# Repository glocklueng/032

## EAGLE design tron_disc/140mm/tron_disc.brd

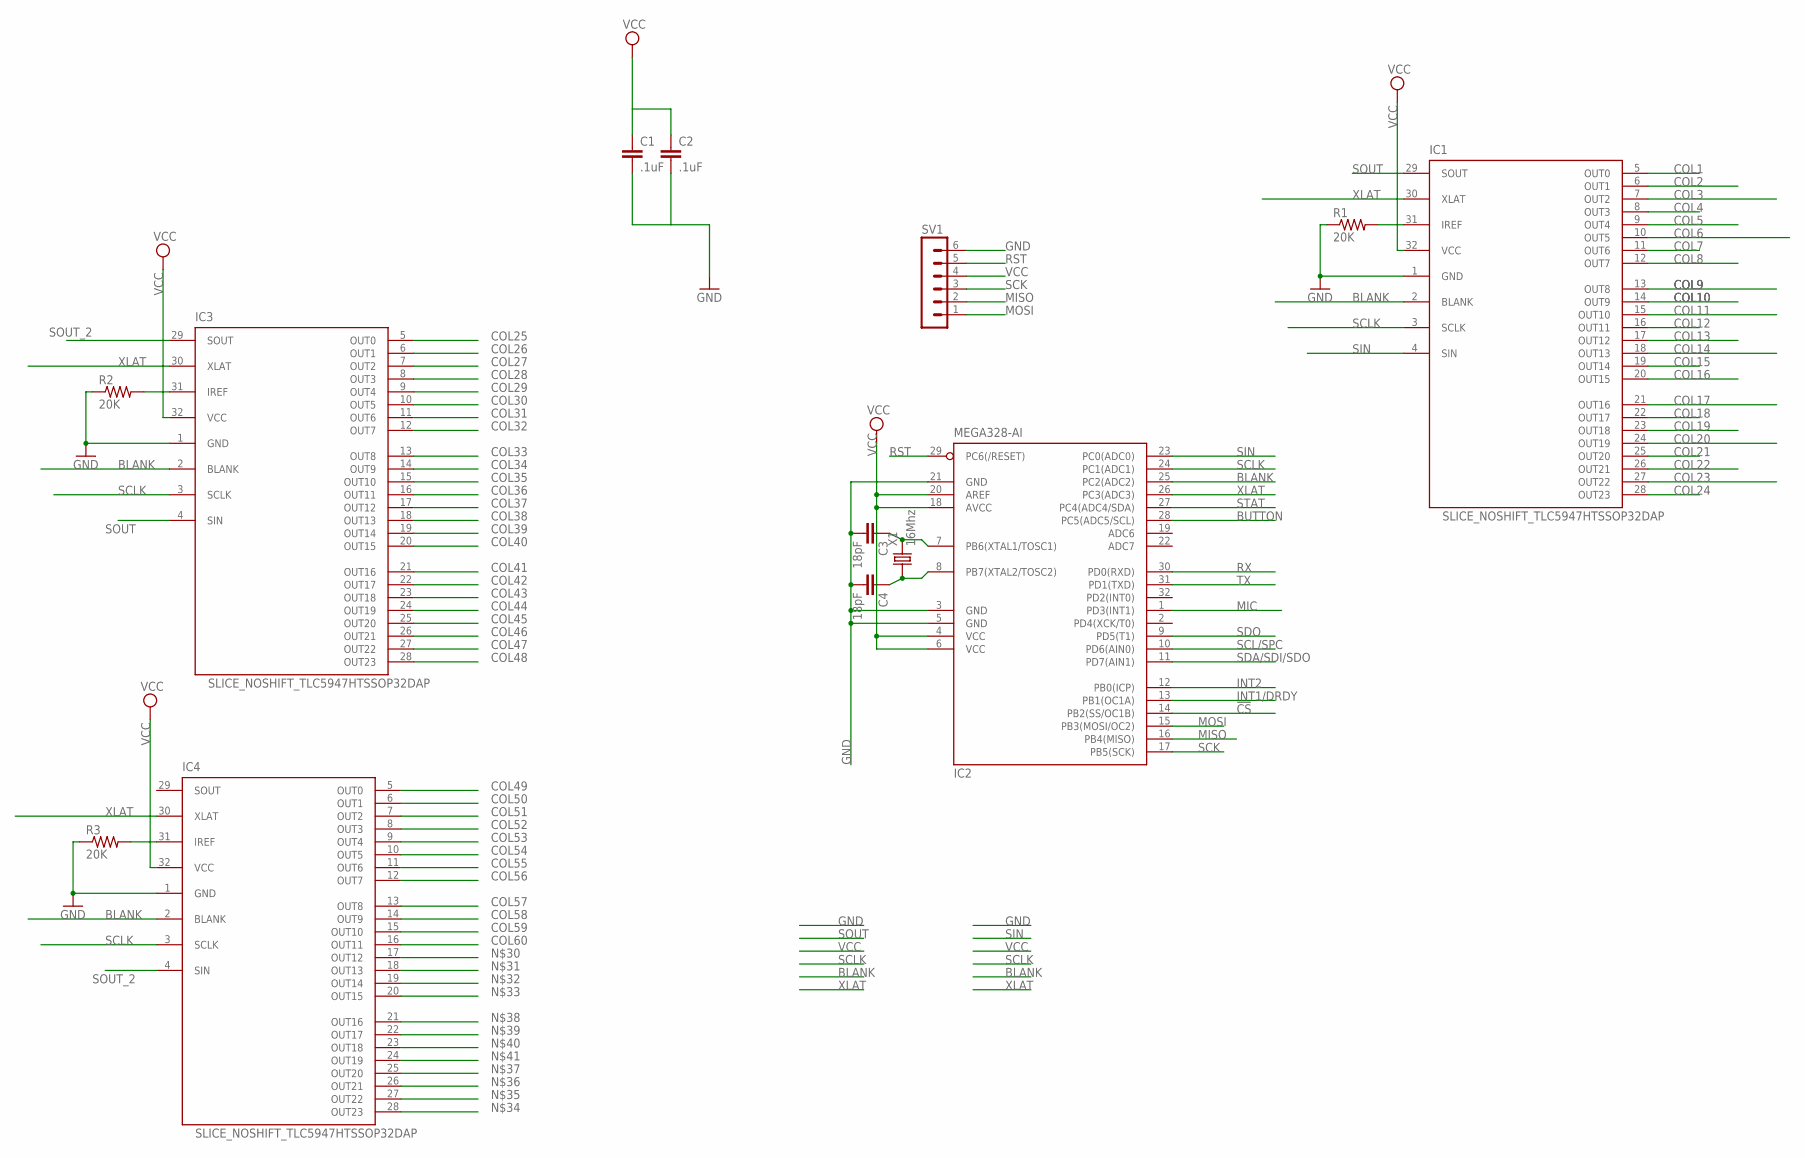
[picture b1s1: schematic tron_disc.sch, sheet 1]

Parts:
C1, C2: .1uF; 0805
C3, C4: 18pF; 0805
IC1, IC3, IC4: SLICE_NOSHIFT_TLC5947HTSSOP32DAP; HTSSOP32DAP
IC2: MEGA328-AI; TQFP32-08
R1, R2, R3: 20K; R0805
SV1: MA06-1
X1: 16Mhz; 5032

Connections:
!CS: IC2.14 (PB2(SS/OC1B))
BLANK: IC1.2 (BLANK), IC2.25 (PC2(ADC2)), IC3.2 (BLANK), IC4.2 (BLANK)
BUTTON: IC2.28 (PC5(ADC5/SCL)); also elsewhere on the board
COL1: IC1.5 (OUT0); also elsewhere on the board
COL2: IC1.6 (OUT1); also elsewhere on the board
COL3: IC1.7 (OUT2); also elsewhere on the board
COL4: IC1.8 (OUT3); also elsewhere on the board
COL5: IC1.9 (OUT4); also elsewhere on the board
COL6: IC1.10 (OUT5); also elsewhere on the board
COL7: IC1.11 (OUT6); also elsewhere on the board
COL8: IC1.12 (OUT7); also elsewhere on the board
COL9: IC1.13 (OUT8); also elsewhere on the board
COL10: IC1.14 (OUT9); also elsewhere on the board
COL11: IC1.15 (OUT10); also elsewhere on the board
COL12: IC1.16 (OUT11); also elsewhere on the board
COL13: IC1.17 (OUT12); also elsewhere on the board
COL14: IC1.18 (OUT13); also elsewhere on the board
COL15: IC1.19 (OUT14); also elsewhere on the board
COL16: IC1.20 (OUT15); also elsewhere on the board
COL17: IC1.21 (OUT16); also elsewhere on the board
COL18: IC1.22 (OUT17); also elsewhere on the board
COL19: IC1.23 (OUT18); also elsewhere on the board
COL20: IC1.24 (OUT19); also elsewhere on the board
COL21: IC1.25 (OUT20); also elsewhere on the board
COL22: IC1.26 (OUT21); also elsewhere on the board
COL23: IC1.27 (OUT22); also elsewhere on the board
COL24: IC1.28 (OUT23); also elsewhere on the board
COL25: IC3.5 (OUT0); also elsewhere on the board
COL26: IC3.6 (OUT1); also elsewhere on the board
COL27: IC3.7 (OUT2); also elsewhere on the board
COL28: IC3.8 (OUT3); also elsewhere on the board
COL29: IC3.9 (OUT4); also elsewhere on the board
COL30: IC3.10 (OUT5); also elsewhere on the board
COL31: IC3.11 (OUT6); also elsewhere on the board
COL32: IC3.12 (OUT7); also elsewhere on the board
COL33: IC3.13 (OUT8); also elsewhere on the board
COL34: IC3.14 (OUT9); also elsewhere on the board
COL35: IC3.15 (OUT10); also elsewhere on the board
COL36: IC3.16 (OUT11); also elsewhere on the board
COL37: IC3.17 (OUT12); also elsewhere on the board
COL38: IC3.18 (OUT13); also elsewhere on the board
COL39: IC3.19 (OUT14); also elsewhere on the board
COL40: IC3.20 (OUT15); also elsewhere on the board
COL41: IC3.21 (OUT16); also elsewhere on the board
COL42: IC3.22 (OUT17); also elsewhere on the board
COL43: IC3.23 (OUT18); also elsewhere on the board
COL44: IC3.24 (OUT19); also elsewhere on the board
COL45: IC3.25 (OUT20); also elsewhere on the board
COL46: IC3.26 (OUT21); also elsewhere on the board
COL47: IC3.27 (OUT22); also elsewhere on the board
COL48: IC3.28 (OUT23); also elsewhere on the board
COL49: IC4.5 (OUT0); also elsewhere on the board
COL50: IC4.6 (OUT1); also elsewhere on the board
COL51: IC4.7 (OUT2); also elsewhere on the board
COL52: IC4.8 (OUT3); also elsewhere on the board
COL53: IC4.9 (OUT4); also elsewhere on the board
COL54: IC4.10 (OUT5); also elsewhere on the board
COL55: IC4.11 (OUT6); also elsewhere on the board
COL56: IC4.12 (OUT7); also elsewhere on the board
COL57: IC4.13 (OUT8); also elsewhere on the board
COL58: IC4.14 (OUT9); also elsewhere on the board
COL59: IC4.15 (OUT10); also elsewhere on the board
COL60: IC4.16 (OUT11); also elsewhere on the board
GND: C1.2, C2.2, C3.2, C4.2, IC1.1 (GND), IC2.3 (GND), IC2.5 (GND), IC2.21 (GND), IC3.1 (GND), IC4.1 (GND), R1.1, R2.1, R3.1, SV1.6; also elsewhere on the board
INT1/DRDY: IC2.13 (PB1(OC1A))
INT2: IC2.12 (PB0(ICP))
MIC: IC2.1 (PD3(INT1))
MISO: IC2.16 (PB4(MISO)), SV1.2
MOSI: IC2.15 (PB3(MOSI/OC2)), SV1.1
unnamed: IC3.31 (IREF), R2.2
unnamed: C3.1, IC2.7 (PB6(XTAL1/TOSC1)), X1.2
unnamed: C4.1, IC2.8 (PB7(XTAL2/TOSC2)), X1.1
unnamed: IC1.31 (IREF), R1.2
unnamed: IC4.31 (IREF), R3.2
RST: IC2.29 (PC6(/RESET)), SV1.5; also elsewhere on the board
RX: IC2.30 (PD0(RXD))
SCK: IC2.17 (PB5(SCK)), SV1.3
SCL/SPC: IC2.10 (PD6(AIN0))
SCLK: IC1.3 (SCLK), IC2.24 (PC1(ADC1)), IC3.3 (SCLK), IC4.3 (SCLK)
SDA/SDI/SDO: IC2.11 (PD7(AIN1))
SDO: IC2.9 (PD5(T1))
SIN: IC1.4 (SIN), IC2.23 (PC0(ADC0))
SOUT: IC1.29 (SOUT), IC3.4 (SIN)
SOUT_2: IC3.29 (SOUT), IC4.4 (SIN)
STAT: IC2.27 (PC4(ADC4/SDA))
TX: IC2.31 (PD1(TXD))
VCC: C1.1, C2.1, IC1.32 (VCC), IC2.4 (VCC), IC2.6 (VCC), IC2.18 (AVCC), IC2.20 (AREF), IC3.32 (VCC), IC4.32 (VCC), SV1.4; also elsewhere on the board
XLAT: IC1.30 (XLAT), IC2.26 (PC3(ADC3)), IC3.30 (XLAT), IC4.30 (XLAT)

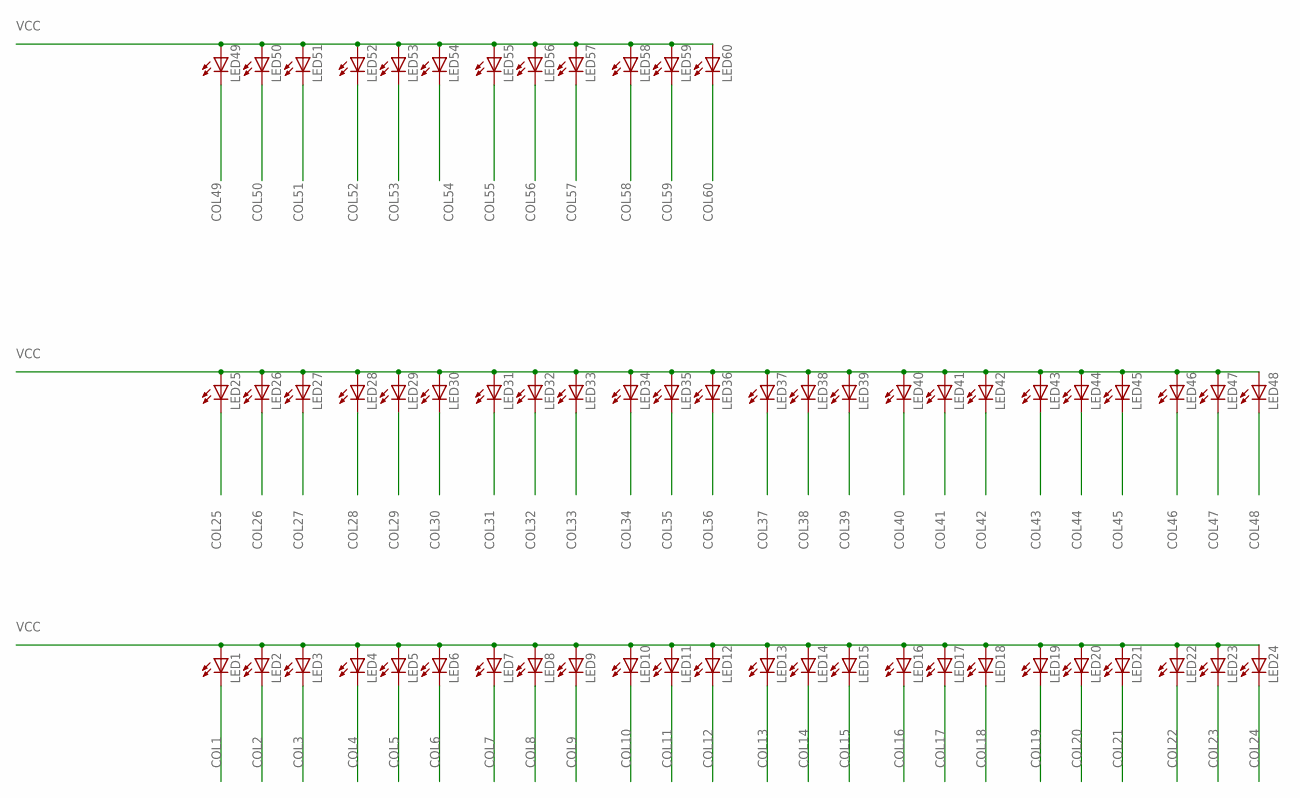
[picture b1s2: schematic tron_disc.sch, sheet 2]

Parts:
LED1, LED2, LED3, LED4, LED5, LED6, LED7, LED8, LED9, LED10, LED11, LED12, LED13, LED14, LED15, LED16, LED17, LED18, LED19, LED20, LED21, LED22, LED23, LED24, LED25, LED26, LED27, LED28, LED29, LED30, LED31, LED32, LED33, LED34, LED35, LED36, LED37, LED38, LED39, LED40, LED41, LED42, LED43, LED44, LED45, LED46, LED47, LED48, LED49, LED50, LED51, LED52, LED53, LED54, LED55, LED56, LED57, LED58, LED59, LED60: LEDCHIPLED_1206; CHIPLED_1206

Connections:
COL1: LED1.C; also elsewhere on the board
COL2: LED2.C; also elsewhere on the board
COL3: LED3.C; also elsewhere on the board
COL4: LED4.C; also elsewhere on the board
COL5: LED5.C; also elsewhere on the board
COL6: LED6.C; also elsewhere on the board
COL7: LED7.C; also elsewhere on the board
COL8: LED8.C; also elsewhere on the board
COL9: LED9.C; also elsewhere on the board
COL10: LED10.C; also elsewhere on the board
COL11: LED11.C; also elsewhere on the board
COL12: LED12.C; also elsewhere on the board
COL13: LED13.C; also elsewhere on the board
COL14: LED14.C; also elsewhere on the board
COL15: LED15.C; also elsewhere on the board
COL16: LED16.C; also elsewhere on the board
COL17: LED17.C; also elsewhere on the board
COL18: LED18.C; also elsewhere on the board
COL19: LED19.C; also elsewhere on the board
COL20: LED20.C; also elsewhere on the board
COL21: LED21.C; also elsewhere on the board
COL22: LED22.C; also elsewhere on the board
COL23: LED23.C; also elsewhere on the board
COL24: LED24.C; also elsewhere on the board
COL25: LED25.C; also elsewhere on the board
COL26: LED26.C; also elsewhere on the board
COL27: LED27.C; also elsewhere on the board
COL28: LED28.C; also elsewhere on the board
COL29: LED29.C; also elsewhere on the board
COL30: LED30.C; also elsewhere on the board
COL31: LED31.C; also elsewhere on the board
COL32: LED32.C; also elsewhere on the board
COL33: LED33.C; also elsewhere on the board
COL34: LED34.C; also elsewhere on the board
COL35: LED35.C; also elsewhere on the board
COL36: LED36.C; also elsewhere on the board
COL37: LED37.C; also elsewhere on the board
COL38: LED38.C; also elsewhere on the board
COL39: LED39.C; also elsewhere on the board
COL40: LED40.C; also elsewhere on the board
COL41: LED41.C; also elsewhere on the board
COL42: LED42.C; also elsewhere on the board
COL43: LED43.C; also elsewhere on the board
COL44: LED44.C; also elsewhere on the board
COL45: LED45.C; also elsewhere on the board
COL46: LED46.C; also elsewhere on the board
COL47: LED47.C; also elsewhere on the board
COL48: LED48.C; also elsewhere on the board
COL49: LED49.C; also elsewhere on the board
COL50: LED50.C; also elsewhere on the board
COL51: LED51.C; also elsewhere on the board
COL52: LED52.C; also elsewhere on the board
COL53: LED53.C; also elsewhere on the board
COL54: LED54.C; also elsewhere on the board
COL55: LED55.C; also elsewhere on the board
COL56: LED56.C; also elsewhere on the board
COL57: LED57.C; also elsewhere on the board
COL58: LED58.C; also elsewhere on the board
COL59: LED59.C; also elsewhere on the board
COL60: LED60.C; also elsewhere on the board
VCC: LED1.A, LED2.A, LED3.A, LED4.A, LED5.A, LED6.A, LED7.A, LED8.A, LED9.A, LED10.A, LED11.A, LED12.A, LED13.A, LED14.A, LED15.A, LED16.A, LED17.A, LED18.A, LED19.A, LED20.A, LED21.A, LED22.A, LED23.A, LED24.A, LED25.A, LED26.A, LED27.A, LED28.A, LED29.A, LED30.A, LED31.A, LED32.A, LED33.A, LED34.A, LED35.A, LED36.A, LED37.A, LED38.A, LED39.A, LED40.A, LED41.A, LED42.A, LED43.A, LED44.A, LED45.A, LED46.A, LED47.A, LED48.A, LED49.A, LED50.A, LED51.A, LED52.A, LED53.A, LED54.A, LED55.A, LED56.A, LED57.A, LED58.A, LED59.A, LED60.A; also elsewhere on the board

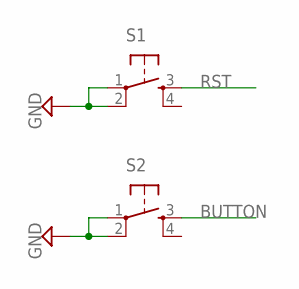
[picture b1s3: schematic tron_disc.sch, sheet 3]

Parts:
S1, S2: TAC_SWITCHSMD; TACTILE_SWITCH_SMD

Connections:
BUTTON: S2.3; also elsewhere on the board
GND: S1.1, S1.2, S2.1, S2.2; also elsewhere on the board
RST: S1.3; also elsewhere on the board

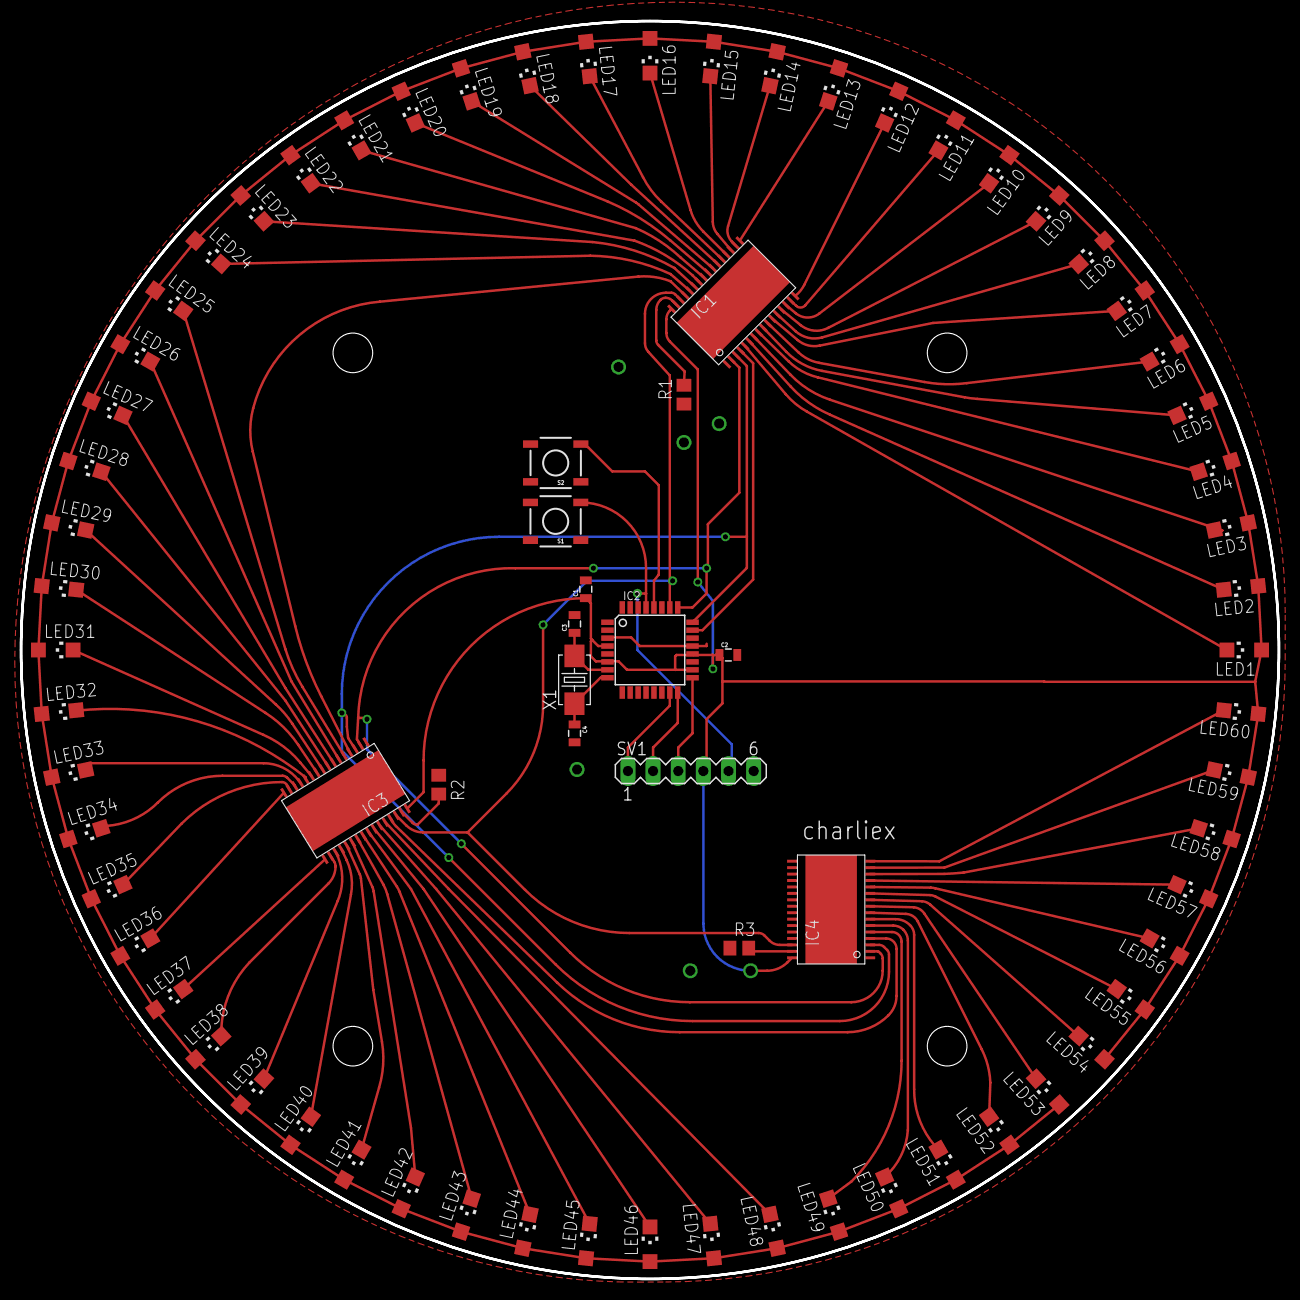
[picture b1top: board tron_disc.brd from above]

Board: 2 copper layers, 127.0 x 127.0 mm, 75 parts (0 on the bottom side), 78 nets.
